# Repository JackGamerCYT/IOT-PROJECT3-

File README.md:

# ⚡ Smart Energy Monitoring & Intelligent Load Management — IoT Project 03

Hệ thống IoT end-to-end: ESP32-S3 đo dòng DC bằng ACS712, tính công suất và điện năng, tự sa thải tải ưu tiên thấp khi vượt ngưỡng đỉnh, gửi dữ liệu qua MQTT về backend FastAPI + cơ sở dữ liệu chuỗi thời gian, hiển thị trên dashboard web thời gian thực kèm trợ lý dữ liệu.

```
 [Adapter 12V]─[cầu chì 2A]─┬─[LM2596 → 5V]──> ESP32-S3, ACS712, relay, OLED, DS3231
                            └─[ACS712 IP+→IP−]─┬─[Relay1]── Quạt 12V  (ưu tiên CAO)
                                               └─[Relay2]── LED 12V   (ưu tiên THẤP)
 ESP32-S3: đo 4 khối/giây · điều khiển cục bộ 2 s/lần · RTC giữ giờ · đệm 600 bản ghi khi mất mạng
      │ MQTT 1883   smartenergy/node9988/{telemetry,status,state,event,cmd,ack}
      ▼
 Broker MQTT ──WSS 8884──> Dashboard (Vercel): realtime, gửi lệnh, đo độ trễ
      │ MQTT 1883
      ▼
 Backend FastAPI (Render 24/7 hoặc laptop) ── SQLite / PostgreSQL(Neon) ── REST /api/*
                                            └── Trợ lý dữ liệu /api/chat
```

## 1. Đáp ứng yêu cầu đề 3

| Yêu cầu trong đề | Cách làm | Ở đâu |
|---|---|---|
| Đo dòng cách ly, điện áp thấp | ACS712-05B, tải DC 12 V, không chạm điện lưới | §3 |
| ≥ 2 tải điều khiển được | Quạt 12 V (ưu tiên cao) + LED 12 V (ưu tiên thấp) | §3 |
| Ghi rõ định mức và bảo vệ | Cầu chì 2 A, diode flyback, relay 10 A/30 VDC, phân áp ADC | `docs/WIRING.md` |
| Telemetry dòng + công suất/điện năng, nêu công thức, đơn vị, tần số | Trung bình 64 mẫu/250 ms, công suất TB 2 s, tích lũy Wh | §4.1 |
| MQTT topic có cấu trúc, QoS, availability | 6 topic, LWT retained | §5 |
| Time-series DB + REST lịch sử/cấu hình | SQLite hoặc PostgreSQL, 5 bảng, 12 endpoint | §6, §7 |
| Dashboard: công suất tức thời, điện năng tích lũy, lịch sử, chi phí, trạng thái tải, cảnh báo | `index.html` | §7 |
| Quản lý tải theo ưu tiên, khôi phục khi an toàn **ổn định** | Máy trạng thái 3 điều kiện + dự báo công suất | §4.2 |
| Phân biệt trạng thái **yêu cầu** và **đã xác nhận** | `cmd_id` → `ack`, UI hiện Yêu cầu / Xác nhận / độ trễ / timeout | §4.3 |
| **Nâng cao**: phát hiện đỉnh, ngân sách điện năng ngày | `peak_today_w`, `ALARM_OVER_LIMIT`, `budget_wh`, `BUDGET_WARN/EXCEEDED` | §4.2 |
| Hành vi an toàn khi mất mạng | Kết nối lại không chặn, SAFE MODE, RTC giữ giờ, đệm và gửi bù | §4.4 |
| Thí nghiệm: sai số, độ trễ, managed/unmanaged, mất kết nối | `/api/stats`, xuất CSV, bảng kịch bản | §10 |

## 2. Cấu trúc repo

```
firmware/esp32_firmware/
  esp32_firmware.ino        Firmware v20 (ESP32-S3 + ACS712 + relay; DS3231/OLED tuỳ chọn)
  secrets.example.h         Copy thành secrets.h, điền WiFi (đã .gitignore)
backend/
  main.py                   FastAPI + MQTT ingest + SQLite/PostgreSQL + trợ lý dữ liệu
  requirements.txt
index.html                  Dashboard, đặt ở GỐC repo để Vercel phục vụ ngay tại "/"
tools/device_simulator.py   Giả lập ESP32 để test khi chưa có phần cứng
docs/
  WIRING.md                 Sơ đồ đấu nối, an toàn, quy trình hàn
  BAO_CAO_IOT_PROJECT03.docx  Báo cáo đồ án 14 đề mục
  PINOUT.xlsx               Bảng chân + danh mục linh kiện
  TRANG_THAI_TRIEN_KHAI.md  Hiện trạng deploy, cách kiểm chứng, việc còn lại
  KHAC_PHUC_SU_CO.md        Web không nhận dữ liệu: cách đọc Serial và tìm nguyên nhân
render.yaml                 Cấu hình deploy backend lên Render
PUSH.md                     Hướng dẫn đẩy code lên GitHub
```

## 3. Phần cứng

| Linh kiện | Chân | ESP32-S3 | Ghi chú |
|---|---|---|---|
| ACS712-05B | OUT | **GPIO 1** qua phân áp 10 kΩ/20 kΩ | 185 mV/A, 2.5 V tại 0 A |
| Relay 2CH (active LOW) | IN1 / IN2 | **GPIO 12 / 13** | Quạt / LED |
| DS3231 (0x68) | SDA / SCL | **GPIO 8 / 9** | Giữ giờ khi mất WiFi |
| SSD1306 (0x3C) | SDA / SCL | **GPIO 8 / 9** | Chung bus I2C với DS3231 |
| Buzzer qua S8050 | — | **GPIO 14** | `-1` nếu không lắp |
| LM2596 | OUT | 5 V / GND | Chỉnh 5.00 V trước khi cắm chip |

Chi tiết đấu nối, mạch động lực, an toàn: `docs/WIRING.md`.

## 4. Firmware v20

### 4.1 Đo lường
- Mỗi 250 ms đọc 64 mẫu `analogReadMilliVolts()` (dùng hiệu chuẩn eFuse của chip), lấy trung bình → `V_out = mV / DIVIDER_RATIO`
- `I [A] = (V_out − V_zero) / 185`; nếu `I < 0.04 A` coi bằng 0 (nhiễu nền). `V_zero` calib lúc khởi động khi 2 tải tắt, hoặc bằng lệnh `calibrate`
- `P [W] = 12 V × I` (điện áp coi là hằng, đo kiểm bằng VOM — ghi trong phần hạn chế)
- `E [Wh] += P × Δt/3600` mỗi khối, lưu Flash mỗi 60 s, reset lúc 0h theo giờ địa phương
- `power_w` gửi lên là **trung bình 2 s** (8 khối); telemetry và vòng điều khiển cùng chu kỳ 2 s

### 4.2 Máy trạng thái quản lý tải
```
LED_ON ──(P > P_peak liên tục ≥ 4 s)──> SHED_PEAK
SHED_PEAK ──(P < P_peak − H liên tục ≥ 15 s  VÀ  LED đã tắt ≥ 20 s
             VÀ  P + P_LED_ước_lượng < P_peak)──> LED_ON
LED_ON ──(E_hôm_nay ≥ ngân sách)──> SHED_BUDGET ──(sang ngày mới)──> LED_ON
LED đã tắt mà vẫn vượt ngưỡng ≥ 10 s → ALARM_OVER_LIMIT + buzzer (quạt ưu tiên cao KHÔNG bị cắt)
```
`P_LED_ước_lượng` được học từ bước nhảy công suất mỗi lần LED đổi trạng thái, nhờ vậy thiết bị không khôi phục khi biết chắc sẽ vượt ngưỡng lại. Ba điều kiện cùng lúc (trễ theo công suất, thời gian tắt tối thiểu, dự báo) là cơ chế chống đóng cắt liên tục.

### 4.3 Lệnh và xác nhận
Web/backend publish `cmd` kèm `cmd_id`. ESP32 áp dụng, publish `ack` chứa `cmd_id` và **trạng thái thực tế** sau khi áp dụng. Dashboard hiển thị riêng "Yêu cầu" và "Xác nhận", đo độ trễ, báo timeout sau 5 s. Bật/tắt tay khi đang AUTO sẽ chuyển thiết bị về MANUAL và sinh sự kiện `MANUAL_OVERRIDE`.

### 4.4 Khi mất mạng
- Kết nối lại WiFi/MQTT không chặn vòng lặp chính → đo và điều khiển vẫn chạy
- Mất broker > 30 s → `safe_mode = true`, tự bật quản lý tải cục bộ dù đang MANUAL
- DS3231 giữ giờ, nên bản ghi vẫn có mốc thời gian đúng; NTP → RTC mỗi 10 phút khi online
- Bộ đệm vòng 600 bản ghi (~20 phút). Có mạng lại thì gửi bù 5 gói/200 ms, gói bù có cờ `"buffered": true` và backend dùng `ts` của thiết bị làm mốc thời gian
- Kết nối lại sinh sự kiện `RECOVERED` kèm thời gian mất kết nối và số gói gửi bù

### 4.5 Nạp firmware
1. Arduino IDE, board **ESP32S3 Dev Module**
2. Library Manager cài **2 thư viện**: `PubSubClient` và `ArduinoJson`
3. Copy `secrets.example.h` → `secrets.h`, điền WiFi
4. Firmware mặc định `USE_RTC 0` / `USE_OLED 0` — chạy được khi **chưa gắn** DS3231 và OLED. Khi nào gắn thì đổi thành `1` và cài thêm `RTClib`, `Adafruit SSD1306`, `Adafruit GFX Library`
5. Có lắp phân áp thì đặt `DIVIDER_RATIO = 0.6667`
6. Upload, mở Serial 115200, **giữ 2 tải tắt** trong 1 giây đầu để calib điểm 0

## 5. Đặc tả MQTT

Gốc topic `smartenergy/<device_id>/`, mặc định `device_id = node9988`.

| Topic | Hướng | QoS / retain | Nội dung |
|---|---|---|---|
| `telemetry` | ESP32 → | 0 | số liệu đo, 2 s/lần |
| `status` | ESP32 → | LWT QoS 1, retained | `online` / `offline` |
| `state` | ESP32 → | retained | cấu hình + trạng thái tải |
| `event` | ESP32 → | 0 | `{type, detail, power_w, limit_w, ts}` |
| `cmd` | web/backend → ESP32 | 1 | `{cmd_id, ts, src, fan?, led?, auto_mode?, peak_limit_w?, hysteresis_w?, budget_wh?, calibrate?, reset_energy?}` |
| `ack` | ESP32 → | 0 | `{cmd_id, cmd_ts, ok, error?, ...state}` |

```json
{"dev":"node9988","ts":1789550319106,"seq":42,"current_a":0.352,"power_w":4.224,
 "energy_today_wh":0.0931,"energy_total_wh":1.204,"peak_today_w":4.301,
 "fan":true,"led":true,"led_shed":"NONE","auto_mode":true,"safe_mode":false,
 "peak_limit_w":3.5,"hysteresis_w":0.5,"budget_wh":0,"led_est_w":1.8,
 "alarm_over":false,"alarm_budget":false,"sensor_mv":2565.1,"zero_mv":2500.0,
 "rssi":-55,"uptime_s":84,"time_src":"ntp","rtc":true,"buffered_count":0}
```

Lý do chọn QoS: telemetry QoS 0 vì gói sau thay gói trước và mất gói được phát hiện qua `seq`; lệnh QoS 1 để không mất lệnh. PubSubClient chỉ publish được QoS 0, nên độ tin cậy của lệnh được bảo đảm ở tầng ứng dụng bằng ACK + timeout 5 s (ghi trong phần hạn chế).

Các loại sự kiện: `SHED`, `RESTORE`, `ALARM_OVER_LIMIT`, `ALARM_CLEAR`, `BUDGET_WARN`, `BUDGET_EXCEEDED`, `MANUAL_OVERRIDE`, `RECOVERED`.

## 6. Cơ sở dữ liệu

Backend tự chọn: có biến `DATABASE_URL` → PostgreSQL (Neon), không có → SQLite. Schema giống nhau, tạo tự động lần chạy đầu.

| Bảng | Cột chính |
|---|---|
| `telemetry` | ts_device, ts_server, seq, current_a, power_w, energy_today_wh, energy_total_wh, peak_today_w, fan, led, led_shed, auto_mode, safe_mode, peak_limit_w, hysteresis_w, budget_wh, alarm_over, alarm_budget, sensor_mv, rssi |
| `events` | ts_device, ts_server, type, detail, power_w, limit_w |
| `availability` | ts_server, status |
| `commands` | cmd_id, source, payload, ts_client, ts_seen_server, ts_ack_server, ack_ok, ack_error, ack_state, latency_ms |
| `settings` | tariff_vnd_per_kwh |

Dữ liệu cũ hơn `RETENTION_DAYS` (mặc định 60) được xóa tự động mỗi 6 giờ.

## 7. REST API (tài liệu tự sinh tại `/docs`)

| Method | Path | Mô tả |
|---|---|---|
| GET | `/api/health` | Trạng thái backend, broker, loại CSDL |
| GET | `/api/status` | Telemetry mới nhất, online/offline, độ tươi dữ liệu, Wh và chi phí hôm nay |
| GET | `/api/history?minutes=&bucket_s=` | Chuỗi thời gian đã gộp (trung bình/đỉnh) |
| GET | `/api/energy/daily?days=` | Wh, đỉnh, chi phí theo ngày |
| GET | `/api/events`, `/api/availability`, `/api/commands` | Nhật ký |
| POST | `/api/command` | `{"fan":true,"wait_ack_s":3}` → trả `requested` và `confirmed` |
| POST | `/api/config` | Ngưỡng, dải trễ, ngân sách, chế độ auto |
| GET/PUT | `/api/settings` | Đơn giá điện |
| GET | `/api/stats?minutes=` | Đỉnh, Wh, thời gian vượt ngưỡng, số lần đóng cắt, tỉ lệ nhận gói, độ trễ |
| POST | `/api/chat` | Trợ lý dữ liệu (§8) |
| GET | `/api/export/{bảng}.csv` | Xuất dữ liệu cho báo cáo |

Khi đặt biến `API_KEY`, mọi POST/PUT phải kèm header `X-API-Key`.

## 8. Trợ lý dữ liệu (chatbot)

Chạy hoàn toàn cục bộ, không gọi API bên ngoài: câu hỏi được chuẩn hoá (bỏ dấu), phân loại ý định bằng biểu thức chính quy, rồi **truy vấn thẳng cơ sở dữ liệu** và ghép câu trả lời từ số liệu thật. Vì không sinh văn bản tự do nên không có nguy cơ bịa số.

Ví dụ hỏi được: *hôm nay dùng bao nhiêu điện*, *tiền điện 7 ngày qua*, *đỉnh công suất hôm nay*, *sa thải tải mấy lần*, *thiết bị offline lúc nào*, *lệnh điều khiển gần đây*, *trạng thái hiện tại*, *so sánh theo ngày*.

Ra lệnh được: *bật quạt*, *tắt đèn*, *bật chế độ tự động*, *đặt ngưỡng 3.5 W*, *đặt ngân sách 20 Wh*. Những câu này **không tự thực thi**: backend trả về trường `action`, dashboard hiện nút "Xác nhận gửi lệnh", người dùng bấm thì mới gọi `/api/command`. Đây là ràng buộc an toàn bắt buộc khi cho ngôn ngữ tự nhiên điều khiển relay.

## 9. Chạy và triển khai

### 9.1 Chạy trên máy (phát triển và demo)
```bash
cd backend
pip install -r requirements.txt
python main.py                       # http://localhost:8000
python ../tools/device_simulator.py  # tuỳ chọn: giả lập ESP32 khi chưa có mạch
```

### 9.2 Hiện trạng triển khai (cập nhật 23/09/2026)

| Thành phần | Địa chỉ | Trạng thái |
|---|---|---|
| Backend + REST API | https://smart-energy-backend-rrvs.onrender.com | Đang chạy, `"db":"postgres"`, `"mqtt_connected":true` |
| Cơ sở dữ liệu | Neon PostgreSQL (pooled, Singapore) | Đã nối, bảng tạo tự động |
| Broker | broker.hivemq.com — TCP 1883 (thiết bị/backend), WSS 8884 (web) | Công khai, không xác thực |
| Dashboard | Vercel, deploy từ `index.html` ở gốc repo | Đang chạy |
| Repo | https://github.com/JackGamerCYT/IOT-PROJECT3- | — |

Kiểm tra nhanh toàn tuyến: `/api/health` → `/api/status` → `/api/history?minutes=10` → `/api/export/telemetry.csv?minutes=60` → SQL Editor trên Neon.

### 9.3 Các bước triển khai lại từ đầu: Neon + Render + Vercel
1. **Neon**: tạo project, copy chuỗi **pooled connection** (`...-pooler...?sslmode=require`)
2. **Render**: New → Blueprint → chọn repo (đã có `render.yaml`) → điền `DATABASE_URL` và `API_KEY` → Apply. Mở `<url>/api/health`, phải thấy `"db":"postgres"` và `"mqtt_connected":true`
3. **Vercel**: Add New → Project → Import repo → Framework Preset = Other, Root Directory để trống, Build/Output Command để trống → Deploy (file `index.html` nằm ngay ở gốc repo nên Vercel phục vụ được luôn)
4. Sửa `const DEFAULT_API = '...'` trong `index.html` thành URL Render rồi push lại; dán `API_KEY` vào ô API Key trên dashboard
5. **Chống ngủ**: gói free của Render tắt service sau ~15 phút không có request, kéo theo mất kết nối MQTT. Tạo job trên cron-job.org gọi `<url>/api/health` mỗi 10 phút

Vì sao cần Render: Vercel chỉ chạy hàm serverless sống vài giây mỗi request, không giữ được kết nối MQTT liên tục để hứng telemetry. Kiến trúc vì vậy tách **worker ingest** (Render) khỏi **giao diện** (Vercel).

Biến môi trường backend: `DATABASE_URL`, `API_KEY`, `MQTT_HOST`, `MQTT_PORT`, `MQTT_USER`, `MQTT_PASS`, `DEVICE_ID`, `TZ_OFFSET_H`, `RETENTION_DAYS`, `PORT`.

## 10. Kịch bản thí nghiệm

| # | Thí nghiệm | Cách làm | Số liệu thu |
|---|---|---|---|
| E1 | Sai số đo | Đồng hồ vạn năng/DC meter nối tiếp, 4 trường hợp: không tải, quạt, LED, cả hai; mỗi trường hợp 30 mẫu | Sai số tuyệt đối và %, độ lệch chuẩn |
| E2 | Độ trễ thiết bị → dashboard | Bật tải, đọc ô "Thiết bị → Dashboard" và `latency_device_to_backend_ms` | Trung bình, p95, max |
| E3 | Độ trễ lệnh → xác nhận | Bấm BẬT/TẮT 30 lần | Trung bình, p95, số lệnh timeout |
| E4 | Unmanaged vs managed | 10 phút AUTO tắt với cả 2 tải bật, ngưỡng 3.5 W → `/api/stats`; lặp lại với AUTO bật | Đỉnh W, Wh, `over_limit_duration_s`, `led_switch_count` |
| E5 | Chống đóng cắt liên tục | Đặt ngưỡng sát tổng công suất, so sánh với cấu hình `hysteresis_w = 0.1`, `MIN_OFF_MS = 0` | Số lần đóng cắt trong 10 phút |
| E6 | Mất mạng | Tắt router 60 s khi đang vượt ngưỡng | Thời điểm OFFLINE (LWT), LED vẫn bị cắt cục bộ, sự kiện `RECOVERED`, số gói gửi bù, khoảng trống dữ liệu |
| E7 | Ngân sách ngày | Đặt `budget_wh` nhỏ (0.5 Wh) | Thời điểm `BUDGET_WARN`/`BUDGET_EXCEEDED`, LED bị cắt |
| E8 | Độ trôi của RTC | So giờ DS3231 với NTP sau 24 giờ | Sai lệch giây/ngày |

## 11. Hạn chế và bảo mật

- Broker HiveMQ công khai không có xác thực: ai biết topic đều đọc và gửi lệnh được. Khắc phục bằng HiveMQ Cloud/EMQX có TLS + tài khoản (firmware và backend đã có sẵn `MQTT_USER`/`MQTT_PASS`) và ACL tách quyền topic `cmd`
- `API_KEY` chỉ bảo vệ REST API, không bảo vệ topic MQTT
- Không đo điện áp thật, giả định 12 V cố định; ACS712 5 A có độ phân giải hạn chế với tải nhỏ. Muốn chính xác hơn dùng INA219/INA226 đo cả V và I
- Một cảm biến đo tổng dòng nên công suất từng tải chỉ là ước lượng từ bước nhảy khi đóng cắt
- ESP32 chỉ publish QoS 0; bộ đệm offline nằm trong RAM nên mất khi reset (có thể nâng cấp sang LittleFS)

## 12. Thành viên

| STT | Họ tên | MSSV | Nhiệm vụ |
|---|---|---|---|
| 1 | Đặng Đình Mạnh | 24119055 | |
| 2 | | | |
| 3 | | | |
| 4 | | | |

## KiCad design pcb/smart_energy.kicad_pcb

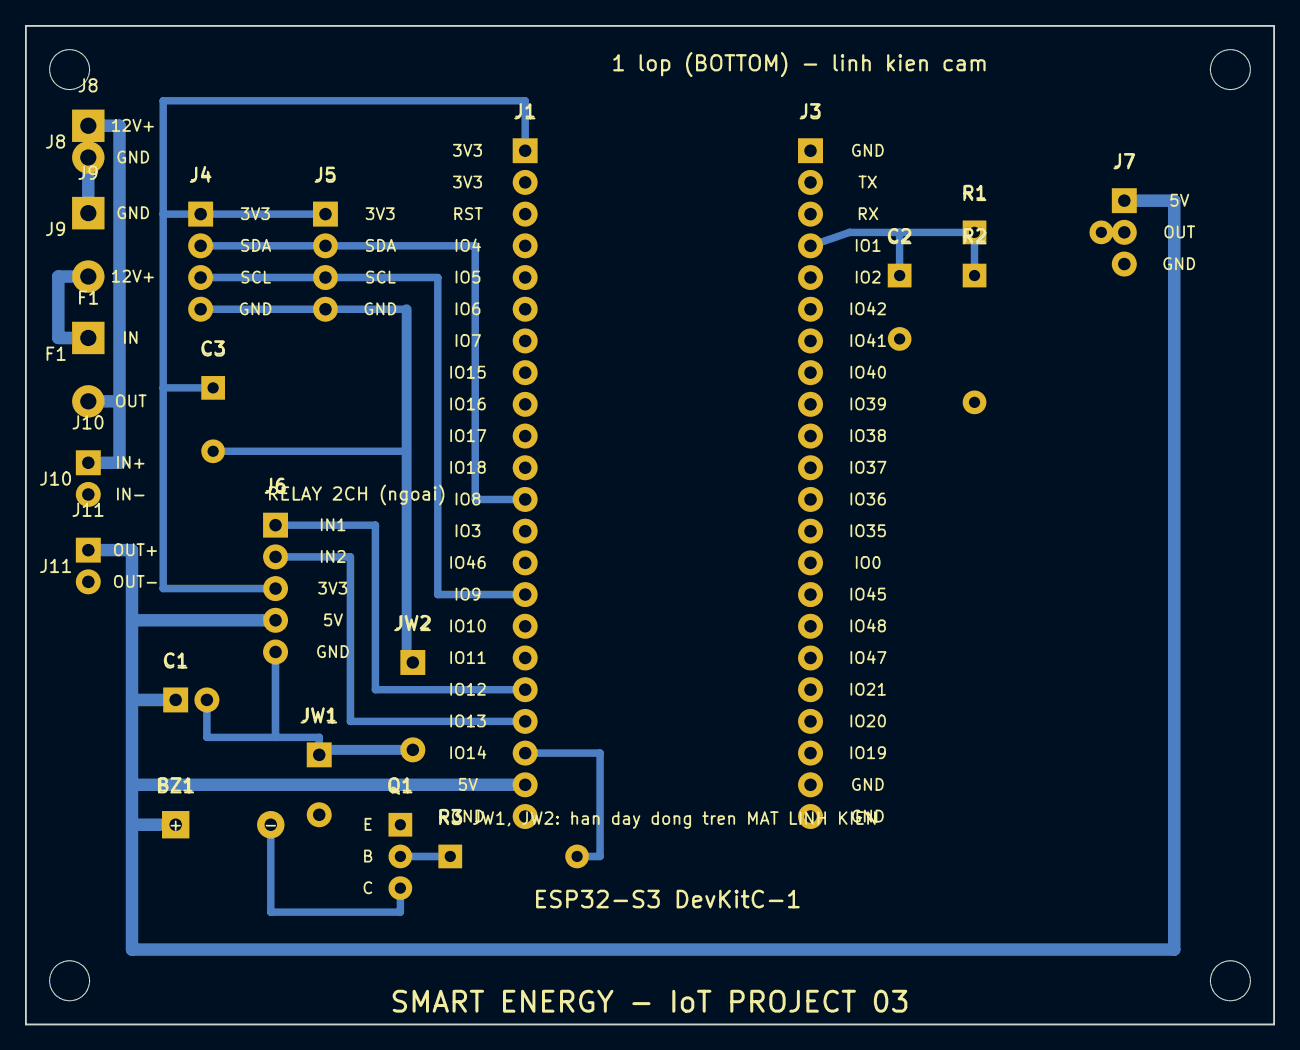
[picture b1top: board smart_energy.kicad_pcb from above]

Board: 2 copper layers, 100.0 x 80.0 mm, 21 parts (0 on the bottom side), 14 nets.

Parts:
BZ1: BUZZER 5V; BZ1
C1: 100uF; C1
C2: 100nF; C2
C3: 100nF; C3
F1: 2A; F1
J1: 1x22; J1
J3: 1x22; J3
J4: 1x4; J4
J5: 1x4; J5
J6: 1x5; J6
J7: 1x3; J7
J8: DOMINO; J8
J9: DOMINO; J9
J10: 1x2; J10
J11: 1x2; J11
JW1: DAY NOI; JW1
JW2: DAY NOI; JW2
Q1: S8050; Q1
R1: 10k; R1
R2: 20k; R2
R3: 1k; R3

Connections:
+3V3: C3.1, J1.1, J4.1, J5.1, J6.3
+5V: BZ1.1, C1.1, J1.21, J6.4, J7.1, J11.1
+12F: F1.2, J8.1, J10.1
+12V: F1.1, J9.2
ACS_OUT: J7.2, R1.2
ADC: C2.1, J3.4, R1.1, R2.1
BUZZ: J1.20, R3.2
BZC: BZ1.2, Q1.3
GND: C1.2, C2.2, C3.2, J1.22, J3.1, J3.21, J3.22, J4.4, J5.4, J6.5, J7.3, J8.2, J9.1, J10.2, J11.2, JW1.1, JW1.2, JW2.1, JW2.2, Q1.1, R2.2
IN1: J1.18, J6.1
IN2: J1.19, J6.2
QB: Q1.2, R3.1
SCL: J1.15, J4.3, J5.3
SDA: J1.12, J4.2, J5.2

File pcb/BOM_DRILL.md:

# Danh sách linh kiện và mũi khoan

| Ref | Giá trị | Mô tả | Số chân | Mũi khoan (mm) |
|---|---|---|---|---|
| J1 | 1x22 | ESP32-S3 DevKitC hàng TRÁI | 22 | 1.0 |
| J3 | 1x22 | ESP32-S3 DevKitC hàng PHẢI | 22 | 1.0 |
| J4 | 1x4 | DS3231 (RTC) | 4 | 1.0 |
| J5 | 1x4 | OLED SSD1306 | 4 | 1.0 |
| J6 | 1x5 | Relay 2 kênh (module ngoài) | 5 | 1.0 |
| J7 | 1x3 | ACS712-05B | 3 | 1.0 |
| R1 | 10k | Phân áp trên | 2 | 0.9 |
| R2 | 20k | Phân áp dưới | 2 | 0.9 |
| C2 | 100nF | Lọc nhiễu ADC | 2 | 0.9 |
| J8 | DOMINO | Ngõ ra 12V đã qua cầu chì | 2 | 1.3 |
| J9 | DOMINO | Nguồn 12V vào | 2 | 1.3 |
| F1 | 2A | Cầu chì (đế 5x20 hoặc dây) | 2 | 1.3 |
| J10 | 1x2 | LM2596 ngõ VÀO (IN+/IN-) | 2 | 1.0 |
| J11 | 1x2 | LM2596 ngõ RA (OUT+/OUT-) | 2 | 1.0 |
| C1 | 100uF | Lọc nguồn 5V | 2 | 1.0 |
| C3 | 100nF | Lọc nguồn 3V3 | 2 | 0.9 |
| JW1 | DAY NOI | Dây nối GND bắc qua đường 5V | 2 | 1.0 |
| JW2 | DAY NOI | Dây nối GND bắc qua 2 đường IN1/IN2 | 2 | 1.0 |
| BZ1 | BUZZER 5V | Còi chíp 5V active | 2 | 1.0 |
| Q1 | S8050 | NPN lái còi (E-B-C) | 3 | 0.9 |
| R3 | 1k | Điện trở cực nền | 2 | 0.9 |
| — | — | Lỗ bắt ốc (4 góc) | 4 | 3.2 |
